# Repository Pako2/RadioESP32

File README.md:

# RadioESP32
RadioESP32 is a high-performance multimedia platform built on the ESP32 architecture. Originally starting as a dedicated standalone internet radio, the platform has evolved significantly. Starting with version 2.0.0, the project has been completely re-engineered into an advanced multi-boot system that transforms a single hardware device into an Internet Radio player, a local SD card audiobook player, and a high-fidelity Bluetooth loudspeaker – all managed by an independent recovery and deployment application.\
**Note:** Complete project documentation can be found in the [UserGuide_EN.pdf](doc/UserGuide_EN.pdf) file.

### Display and embedded web server preview
For illustration, you can see three photos of the display. You may be surprised to see that some of the text lines are blurred. The explanation is simple. This is scrolling text, because otherwise it wouldn't fit on the display!\
The first picture shows the radio playing, the second shows a file playing from an SD card, and the third shows the clock.

There's no need to describe the appearance of the web interface. You can learn much more from a few screenshots.

## Project Origin & Acknowledgments
This project would likely never have been created without the popular [ESP32Radio-V2](https://github.com/Edzelf/ESP32Radio-V2) project by [Edzelf](https://github.com/Edzelf). I am deeply grateful to the author for his outstanding work, which served as the original foundation for this software.

While I initially deployed the original project in its unchanged form, several limitations quickly became apparent. My primary motivation for rewriting and expanding the software stemmed from two major issues:

- **Localization:** The original display implementation did not support accented diacritics, which was critical for a proper local user experience.

- **Audiobook Playback:** One of my core requirements was the ability to listen to audiobooks from an SD card. Audiobooks require files to be played in a strict, defined alphabetical order. In the original software, copying files from a PC to an SD card resulted in them being indexed and played in a seemingly random order, making sequential listening highly complicated without constant manual track selection.

Additionally, I preferred a different default behavior. Instead of always resuming the last played station at the previous volume level upon power-up, I prefer the device to initialize to a pre-defined default station and default volume. I also planned to integrate entirely new hardware and software features, such as single-button power toggling and an automated sleep/turn-off timer.

Despite these changes, several core elements from Edzelf's project were retained, which significantly aided my early development. Furthermore, the web interface design, the communication method between the ESP32 and the browser, and the configuration file management system were adopted from the [esp-rfid](https://github.com/esprfid/esp-rfid) project - a highly reliable setup I have successfully utilized across multiple designs.

# Evolution in Version 2.0.0+
During development, I realized that with a purely software-driven approach, the existing hardware design could be utilized as a full-featured Bluetooth loudspeaker. To implement this comfortably, version 2.0.0 underwent a fundamental architectural overhaul.
To streamline production and focus on maximum stability, legacy sub-variants (such as designs without a display or designs storing web server assets directly inside a volatile file system partition) were abandoned. Moving forward, the project is maintained as a single production variant: always equipped with a display and always compiling web server assets directly into the program memory. This specific design is mandatory to support the automated multi-boot Update Manager system.

## Upgrading from Version 1.X.X
If you are upgrading an existing device from a 1.X.X release, your configuration file is fully compatible with the new version. However, due to the fundamental architectural changes mentioned above, a clean installation via cable is required:
- **Backup** your current configuration using the Backup & Restore menu in your existing web interface.
- Perform a **full installation** over a USB cable using the new Flash utility (flash.bat).
- **Restore** your configuration file using the Backup & Restore menu in the new version 2.0.0 interface.

**Note:** 
*Before proceeding with the upgrade, please verify that your hardware meets the new minimum requirements (8MB Flash and PSRAM), as legacy 4MB modules are no longer supported.*

## Legacy Differences: Radio Application vs. Edzelf's ESP32Radio
The following enhancements and modifications apply exclusively to the Internet Radio application (and its web configuration) compared to the original Edzelf implementation:

- **Strict Alphabetical Playback:** Fixed the random indexing issue on SD cards. Files and folders are sorted properly, enabling seamless audiobook listening. However, shuffle mode can be turned on as needed.

- **Diacritics & Extended Character Support:** The display engine was rewritten to support full native character mapping and custom fonts.

- **Predictable Initialization:** The device turns on to a user-defined default station and safe volume level rather than resuming the last state.

- **Single-Button Power Toggle:** Hardware-software integration allows turning the entire device completely on and off using the same single physical button.

- **Integrated Sleep Timer:** Supports a configurable sleep countdown that automatically powers down the hardware.

- **Comfortable Web-Based IR Learning:** Unlike the original project, adding or modifying infrared remote control commands is managed through an incredibly intuitive and automated web interface, allowing the device to capture and assign raw hardware codes on the fly.

# Full-Featured Bluetooth Loudspeaker Application
The Bluetooth Loudspeaker mode (running on OTA\_1) is engineered to deliver a premium commercial-grade user experience, offering deep visual feedback and control options rarely found in DIY audio systems.

## Key features include:
- **Identical Display Dashboard:** The physical display mirrors the rich visual interface of the Radio application, showing a real-time battery status indicator, an active volume bar, and a track progress bar.

- **Dynamic Status Icons:** Features clear visual indicators for Bluetooth connectivity (color-coded blue for active connection, grey for disconnected state) along with dedicated Play/Pause status indicators.

- **Rich Metadata & Auto-Scrolling:** Streams live metadata directly from the connected smartphone. Track titles, artist names, and album details are fully processed and rendered with native diacritic support, automatically triggering a smooth text-scrolling engine if the text length exceeds the screen boundaries.

- **Dual Physical Control Layers:** The loudspeaker can be controlled fully via the mechanical physical rotary encoder or completely hands-free using an Infrared Remote Control (handling Play, Pause, Track Skip, and Volume adjustments).

- **Centralized Configuration:** Because the Bluetooth application completely turns off the Wi-Fi stack to eliminate protocol overhead and interference, it does not host a web server. Instead, all Bluetooth-specific settings (including custom broadcast device naming and the advanced IR remote control command learning) are comfortably configured inside the unified web interface of the Internet Radio application.

# System Architecture & Multi-Boot Partitioning
Due to the strict hardware limitations of the ESP32 chip (specifically the high instability and memory constraints of running Wi-Fi and Bluetooth stacks simultaneously) the system separates core features into completely independent firmware binaries.

The system utilizes a custom partition layout designed for 8MB Flash chips. The minimum required hardware configuration is the ESP32-WROVER-E-N8R4 module. Volatile PSRAM memory is mandatory, as modern versions of the underlying audio libraries will not function without it.

## The memory layout divides the hardware into four distinct primary zones:
| Partition Type | Application Name | Core Functionality | Network State |
| - | - | - | - |
| **Factory** | Update Manager | Recovery, deployment, and binary flashing | Wi-Fi (Station with Internet) |
| **OTA\_0** | Internet Radio | Web-streaming, SD card media player | Wi-Fi (Station / Initial AP Setup) |
| **OTA\_1** | BT Loudspeaker | High-fidelity A2DP audio playback | Completely Disabled (No Wi-Fi) |
| **LittleFS** | Configuration | Shared system settings and profiles | Non-volatile storage |

All three applications share a single, unified configuration file stored in the LittleFS zone. Switching between applications triggers a low-level hardware reset using direct RTC controller registry manipulation, ensuring that the hardware cache and DMA controllers are completely cleared for a pure warm boot.

# Independent Update Manager
Because individual OTA application partitions contain completely different binary structures (Radio vs. Bluetooth), traditional OTA upgrades (where a new version is uploaded to an inactive slot and toggled) are impossible.

The project solves this by deploying a completely independent recovery application in the factory partition. When triggered via the display menu or the radio's web interface, the device reboots into the red-themed Update Manager web server (accessible via the credentials defined in the source code). From this dashboard, users can view live tables comparing current firmware versions against the latest versions available online, perform automated network updates, create full system binary backups, or deploy manual downgrades from local files.

### ⚠️ Important Note regarding Over-the-Air (OTA) Web Upgrades

Due to strict modern browser security standards (CORS policies) implemented by GitHub, web browsers will natively block the JavaScript interface from directly transferring firmware files from GitHub Releases onto your local IP address via the single-click "Update" buttons.

To complete an application upgrade, you have two equally reliable options:

1. **Manual Offline Upload (Recommended & Safest):** 
   Simply click the green **Download** button next to the target application to save the latest `.bin` firmware file directly to your PC. Then, navigate to the **Firmware Upload** panel below, select the correct **Target Application**, click the **Browse...** button to select the downloaded binary from your hard drive, and click **Flash Selected File**.

2. **Direct Web Upgrade (Advanced):**
   If you prefer to upgrade with a single click directly from the web interface using the automated table, you must temporarily enable a CORS-bypass extension in your browser (such as *"Allow CORS: Access-Control-Allow-Origin"* for Chrome/Firefox) before opening the Update Manager dashboard.

The Update Manager features critical system-level fail-safes. If the supply battery drops below a safe operational threshold during an update cycle, an asynchronous JavaScript modal hard-locks the entire web interface, preventing user interactions until safe power parameters are restored, eliminating the risk of accidental firmware bricking.

## Advanced Graphics Engineering
To achieve absolute long-term stability, the graphics pipeline was completely refactored. The Bluetooth application runs an aggressive real-time A2DP data sink. Under standard implementations, multi-core thread collisions frequently occur on the shared SPI display bus when high-priority Bluetooth background tasks on Core 0 interrupt the main application execution loop on Core 1.

The system eliminates these race conditions by removing traditional RTOS mutexes entirely. Instead, all graphic subsystems, status readouts, and display bars (such as the volume bar, battery indicator, progress bars, and scrolling metadata tracks) are completely centralized under a single-task, asynchronous flag-driven pipeline in the display loop. Asynchronous events from Bluetooth callbacks merely flag status variables in RAM, which are safely ingested and drawn by a single dedicated display task.

# Development and Build Flags
The project is developed in VS Code using the PlatformIO IDE paired with the Pioarduino extension. Using environment build flags in `platformio.ini`, the firmware behavior is customized using the following core definitions:

- **DATAWEB=true/false:** Setting this flag to `true` compiles a development variant where web server assets are loaded dynamically from the LittleFS partition, allowing real-time, browser-based source editing via the integrated online [Ace editor](https://ace.c9.io/). Setting this to `false` creates the production variant, compressing and injecting all HTML and JS assets directly into the program memory (PROGMEM) as static variables. This is the mandatory format for deployment binaries.

- **SDCARD:** Compiles full support for the local SD card hardware and alphabetical media player engine.

- **BATTERY:** Enables power monitoring, enabling precise voltage calibration routines and rendering live battery status bars across both the physical display and web dashboards.

- **AUTOSHUTDOWN:** Compiles the control logic for the single-button soft power toggle circuit and the automatic sleep timer.

# Third-Party Libraries & Acknowledgments
This project relies heavily on the open-source community. I would like to express my sincere gratitude to the authors of the following exceptional libraries, whose hard work made this multi-boot platform possible:

- **[ESP32-audioI2S](https://github.com/schreibfaul1/ESP32-audioI2S) by schreibfaul1** – The core engine powering the high-performance internet radio streaming and SD card media playback.

- **[ESP32-A2DP](https://github.com/pschatzmann/ESP32-A2DP) by pschatzmann** – The backbone of the Bluetooth application, providing a reliable and robust real-time A2DP audio sink.

- **[ESPAsyncWebServer](https://github.com/ESP32Async/ESPAsyncWebServer)** – Essential for driving the asynchronous, responsive web interfaces across the platform slots.

- **[ArduinoJson](https://github.com/bblanchon/ArduinoJson) by bblanchon** – Used for fast, memory-efficient parsing of configuration files and the update manager tables.

- **[base64](https://github.com/Densaugeo/base64_arduino) by Densaugeo** – Utilized for secure encoding and handling of system assets and network communication data.

- **[Arduino-IRremote](https://github.com/Arduino-IRremote/Arduino-IRremote)** – Powering the automated infrared remote control receiver and code-learning capabilities.

- **[TFT\_eSPI](https://github.com/Bodmer/TFT_espi) by Bodmer** – The highly optimized graphics driver used to render sprites and smooth scrolling text on the SPI display.

- **[U8g2](https://github.com/olikraus/u8g2) by olikraus** & **[U8g2\_for\_TFT\_eSPI](https://github.com/Bodmer/U8g2_for_TFT_eSPI) by Bodmer** – Providing the comprehensive font support required for native localization, accented diacritics, and system icons.

## PlatformIO Environment & Custom Python Targets
The project utilizes advanced customization features of PlatformIO with the Pioarduino extension to automate the compilation, transformation, and deployment of firmware slots. Since standard environment filters naturally restrict automated serial flashing to the `OTA_0` partition, a dedicated set of specialized automation scripts was engineered to streamline the development workflow:

- **`app_deploy.py` (Binary Archiving):** Executed automatically post-build. It automatically moves and renames compiled images into the structured `/bin/<env>/` directory, preparing them for deployment.

- **`custom_targets.py` (Advanced Workflow Automation):** Exposes core system functions accessible comfortably directly via the *Pioarduino: Project Tasks / \<env\> / Custom* IDE side menu. It processes two critical automated workflows:

  - **Download FS & Create WEBH:** Automates the complete transformation of production web assets. It downloads the live file system image from the hardware using maxgerhardt's downloader utility, extracts the HTML and JS assets from `LittleFS`, and translates them directly into compressed C++ array data variables ready for `PROGMEM` generation.

  - **Upload custom binary:** The primary development flashing mechanism. Instead of pushing blindly to `OTA_0`, this target programmatically parses the local partition configuration table, dynamically locates the precise memory address boundaries for the active target environment, and executes a targeted wired upload directly to the correct slot (`OTA_1` for Bluetooth loudspeaker or `factory` for the Update Manager).

## Production Flash Utilities
For initial provisioning, assembly, and bulk deployment outside the VS Code IDE development sandbox, a dedicated, standalone host script named Flash Utilities is used.

This standalone batch utility operates strictly as a master installation tool tailored for two main deployment scenarios:

1. **Full Environment Initialization:** Performs the first-time wired flashing of a fresh, raw ESP32 chip. It writes the global bootloader configurations, custom multi-boot partition boundaries, the initial `LittleFS` shared configuration image, and all three application binaries concurrently.

2. **Targeted Service Upgrades:** Provides a safe serial bypass tool to manually write or restore a single specific slot over a wired serial connection. This is the mandatory path required for initial installation or forced rewrites of the factory recovery application partition without formatting or impacting user profiles.

On a fresh device provisioning cycle, the system triggers a default fallback standalone Wi-Fi Access Point named **RadioESP32**. Navigating a web browser to `192.168.4.1` loads the initial onboarding setup screen to connect the multi-boot hardware platform to local wireless station configurations.

# Hardware Design & Component Selection
The physical hardware architecture is designed using the free/personal-use tier of Autodesk Eagle, utilizing a dual-stage isolation approach to completely eliminate ground loops, digital switching noise, and interference.

### Wiring diagram

### Printed circuit board

### Choice of components
In the first phase of development, I used the VS1053 module (as a DAC) following Edzelf's example. It worked well, but I found this solution unnecessarily expensive and quite problematic (for example, I once accidentally bought a VS1003 instead and it didn't work well). That's why I completely abandoned this path and switched exclusively to a solution with I2S.
- **Main Processor:** ESP32-WROVER-E module (Silicon Revision 3 or higher, minimum 8MB Flash and 4MB PSRAM).

- **Power Supply:** 12V primary input, optimized to run efficiently from three series-connected 18650 Li-ion cells or a standard wall adapter. A high-efficiency Mini560 step-down module regulates this down to a stable 5V rail. The module's EN (Enable) pin is directly wired into the single-button latching circuit for hard physical power management.

- **Audio DAC:** PCM5102A I2S module, selected for its high dynamic range and integrated analog out pin liars, eliminating complex internal chassis cabling.

- **Ground Loop Isolation:** Two low-profile 9.1mm audio isolation transformers are placed inline directly between the DAC outputs and the amplifier inputs, successfully blocking digital hum and cross-talk.

- **Amplifier Stage:** PAM8406 5V stereo amplifier IC. This specific chip was chosen because it can operate in either Class-D (high efficiency for battery operation) or Class-AB (low RF noise for clean radio reception). The operating mode is manually selected on the PCB via hardware jumpers.

- **Display Interface:** 1.77-inch SPI TFT panel (160x128 resolution) driven natively by the optimized TFT\_eSPI library.

- **User Control:** A robust EC11 mechanical rotary encoder with an integrated push-button handles physical navigation, complemented by a VS1838B infrared receiver supporting automatic remote control code learning.

- **Chassis Connections:** Traditional screw terminals were replaced with high-reliability 4.8mm male Faston terminals soldered directly to the PCB for all primary power inputs and speaker outputs, ensuring vibrating-proof connections inside the speaker enclosure.

## Assembled board
Finally, you can see a few pictures of the printed circuit board completely assembled and including the installed subboards (ESP32 development kit and DAC). I also added one photo of the finished radio (powered by three 18650 Li-ion cells).

### License
The code parts written by the author of the **RadioESP32** project are licensed under [GPL-3.0](LICENSE), 3rd party libraries that are used by this project are licensed under different license schemes, please check them out as well.

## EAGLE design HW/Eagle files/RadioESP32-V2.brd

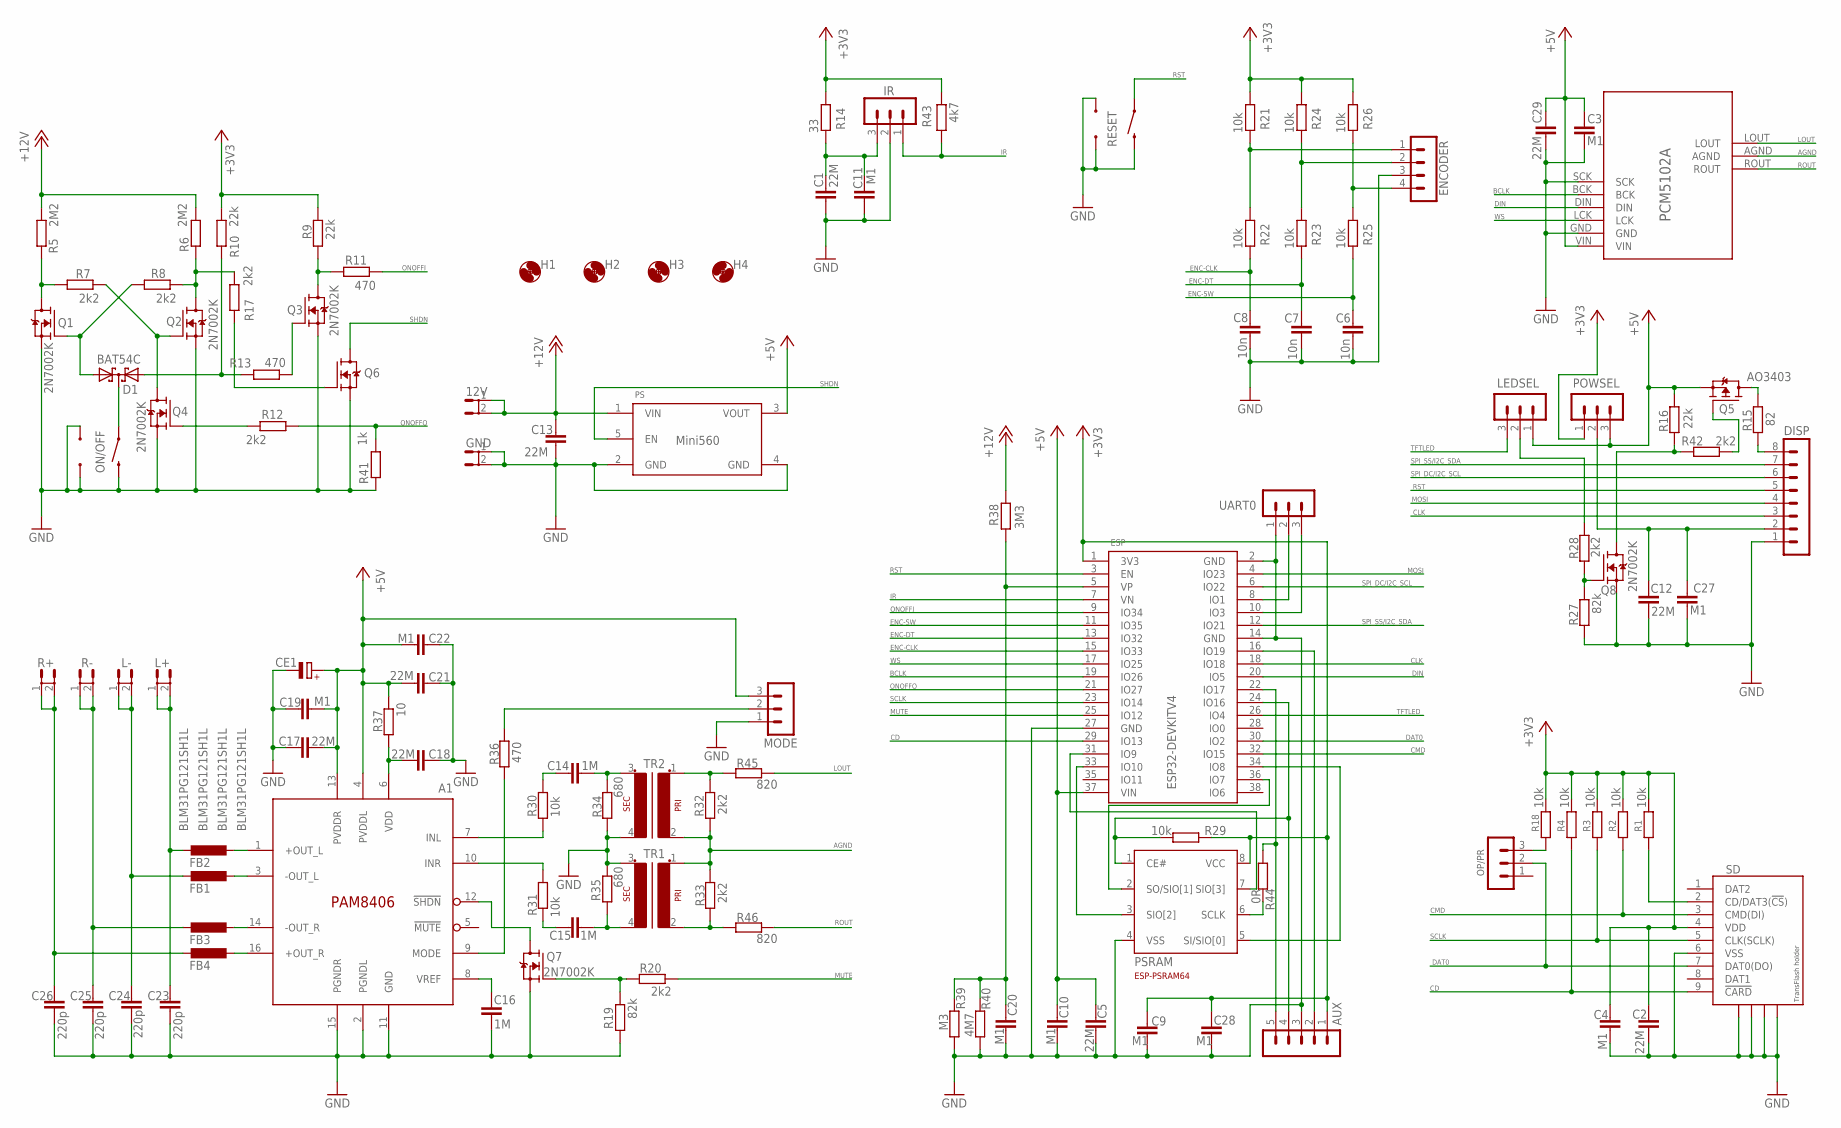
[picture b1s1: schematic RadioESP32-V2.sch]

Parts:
12V: FASTON; FASTON4.8
A1: PAM8406; SOP-16
AUX: CON-LSTB_MA05-108; CON-LSTB_MA05-1-NS08
C1, C2, C5, C12, C13, C17, C18, C21, C29: 22M; C1206K
C3, C4, C9, C10, C11, C19, C20, C22, C27, C28: M1; C0805
C6, C7, C8: 10n; C0805
C14, C15, C16: 1M; C1206K
C23, C24, C25, C26: 220p; C0805
CE1: CPOL; E5-10.5
D1: BAT54C; SOT23
DISP: CON-LSTB_MA08-108; CON-LSTB-MA08-1-NS08
ENCODER: CON-LSTB_MA04-108; CON-LSTB_MA04-1-NS08
ESP: ESP32-DEVKITV4_ESP32DEVKITV4NOTXT; ESP32_DEVKIT_V4
FB1, FB2, FB3, FB4: BLM31PG121SH1L; C1206K
GND: FASTON; FASTON4.8
H1, H2, H3, H4: MOUNT-HOLE3.0; 3,0
IR: CON-LSTB_MA03-108; CON-LSTB_MA03-1-NS08
L+: FASTON; FASTON4.8
L-: FASTON; FASTON4.8
LEDSEL: CON-LSTB_MA03-108; CON-LSTB_MA03-1-NS08
MODE: CON-LSTB_MA03-108; CON-LSTB_MA03-1-NS08
ON/OFF: MOMENTARY-SWITCH-SPST1; TACTILE_SWITCH_ANGLE-NS1
OP/PR: CON-LSTB_MA03-108; CON-LSTB_MA03-1-NS08
PCM5102A: PCM5102A_MODULE
POWSEL: CON-LSTB_MA03-108; CON-LSTB_MA03-1-NS08
PS: MINI560EXT; MINI560-NS-EXT
PSRAM: PSRAM; SOT23-8-W
Q1, Q2, Q3, Q4, Q6, Q7, Q8: 2N7002K; TRANSISTOR-FET_SOT23
Q5: AO3403; SOT23
R1, R2, R3, R4, R18, R21, R22, R23, R24, R25, R26, R29, R30, R31: 10k; R0805
R5, R6: 2M2; R0805
R7, R8, R12, R17, R20, R28, R32, R33, R42: 2k2; R0805
R9, R10, R16: 22k; R0805
R11, R13, R36: 470; R0805
R14: 33; R0805
R15: 82; R1206
R19, R27: 82k; R0805
R34, R35: 680; R0805
R37: 10; R0805
R38: 3M3; R0805
R39: M3; R0805
R40: 4M7; R0805
R41: 1k; R0805
R43: 4k7; R0805
R44: 0R; R0805
R45, R46: 820; R0805
R+: FASTON; FASTON4.8
R-: FASTON; FASTON4.8
RESET: MOMENTARY-SWITCH-SPST1; TACTILE_SWITCH_ANGLE-NS1
SD: SD-MMC_TF-HOLDER; SD-MMC_TF-PULL
TR1, TR2: AUDIOTRAFONS2; AUDIOTRAFO_2-NS
UART0: CON-LSTB_MA03-108; CON-LSTB_MA03-1-NS08

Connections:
+3V3: AUX.1, C2.2, C4.2, C9.2, C28.2, ESP.1 (3V3), POWSEL.1, PSRAM.8 (VCC), R1.2, R2.2, R3.2, R4.2, R9.2, R10.2, R14.2, R18.2, R21.2, R24.2, R26.2, R29.1, R43.1, SD.4 (VDD)
+5V: A1.4 (PVDDL), A1.13 (PVDDR), C3.1, C5.1, C10.1, C17.2, C19.2, C21.1, C22.1, C29.2, CE1.+, CE1.++ (+), ESP.37 (VIN), LEDSEL.1, MODE.3, PCM5102A.VIN, POWSEL.3, PS.3 (VOUT), Q5.2 (S), R16.2, R37.1
+12V: 12V.1, 12V.2, C13.2, PS.1 (VIN), R5.2, R6.2, R38.2
AGND: PCM5102A.AGND, R32.1, R33.2, TR1.1, TR2.2
BCLK: ESP.19 (IO26), PCM5102A.BCK
CD: ESP.29 (IO13), R4.1, SD.9 (!CARD)
CLK: DISP.3, ESP.18 (IO18)
CMD: ESP.32 (IO15), R2.1, SD.3 (CMD(DI))
DAT0: ESP.30 (IO2), OP/PR.2, SD.7 (DAT0(DO))
DIN: ESP.20 (IO5), PCM5102A.DIN
ENC-CLK: C8.1, ESP.15 (IO33), R22.1
ENC-DT: C7.1, ESP.13 (IO32), R23.1
ENC-SW: C6.1, ESP.11 (IO35), R25.1
GND: A1.2 (PGNDL), A1.11 (GND), A1.15 (PGNDR), AUX.3, C1.2, C2.1, C3.2, C4.1, C5.2, C6.2, C7.2, C8.2, C9.1, C10.2, C11.2, C12.1, C13.1, C16.1, C17.1, C18.2, C19.1, C20.1, C21.2, C22.2, C23.1, C24.1, C25.1, C26.1, C27.2, C28.1, C29.1, CE1.-, DISP.1, ENCODER.3 (4), ESP.2 (GND), ESP.14 (GND), ESP.27 (GND), GND.1, GND.2, IR.2, MODE.1, ON/OFF.2, ON/OFF.A1, ON/OFF.A2, PCM5102A.GND, PCM5102A.SCK, PS.2 (GND), PS.4 (GND), PSRAM.4 (VSS), Q1.2 (S), Q2.2 (S), Q3.2 (S), Q4.2 (S), Q6.2 (S), Q7.2 (S), Q8.2 (S), R19.2, R27.2, R34.1, R35.2, R39.1, R40.1, R41.1, RESET.2, RESET.A1, RESET.A2, SD.6 (VSS), SD.S1, SD.S2, SD.S3, SD.S4, TR1.3 (S1), TR2.4 (S2), UART0.1
IR: ESP.7 (VN), IR.1, R43.2
LEDA: DISP.8, R15.1
LOUT: PCM5102A.LOUT, R45.2
MOSI: DISP.4, ESP.4 (IO23)
MUTE: ESP.25 (IO12), R20.1
N31: D1.2 (A2), R10.1, R13.2
unnamed: ESP.36 (IO7), PSRAM.2 (SO/SIO[1])
unnamed: ESP.34 (IO8), PSRAM.5 (SI/SIO[0])
unnamed: C14.1, R34.2, TR2.3 (S1)
unnamed: C15.2, R35.1, TR1.4 (S2)
unnamed: C14.2, R30.2
unnamed: A1.7 (INL), R30.1
unnamed: C15.1, R31.2
unnamed: A1.10 (INR), R31.1
unnamed: C1.1, C11.1, IR.3, R14.1
unnamed: Q2.3 (D), R6.1, R8.1, R17.1
unnamed: Q7.1 (G), R19.1, R20.2
unnamed: ESP.33 (IO10), PSRAM.3 (SIO[2])
unnamed: ESP.31 (IO9), PSRAM.7 (SIO[3])
unnamed: Q3.1 (G), R13.1
unnamed: R1.1, SD.2 (CD/DAT3(!CS!))
unnamed: Q1.3 (D), R5.1, R7.2
unnamed: Q5.1 (G), R42.1
unnamed: D1.3 (CC), ON/OFF.1
unnamed: Q2.1 (G), Q4.3 (D), R7.1
unnamed: D1.1 (A1), Q1.1 (G), R8.2
unnamed: Q4.1 (G), R12.2
unnamed: AUX.4, ESP.24 (IO16), PSRAM.1 (CE#), R29.2
unnamed: Q3.3 (D), R9.1, R11.2
unnamed: PSRAM.6 (SCLK), R44.2
unnamed: AUX.2, ESP.16 (IO19)
unnamed: C12.2, C27.1, DISP.2, POWSEL.2
unnamed: R32.2, R45.1, TR2.1
unnamed: A1.8 (VREF), C16.2
unnamed: A1.12 (!SHDN), Q7.3 (D)
unnamed: A1.9 (MODE), R36.1
unnamed: MODE.2, R36.2
unnamed: C23.2, FB2.2, L+.1, L+.2
unnamed: R33.1, R46.1, TR1.2
unnamed: C25.2, FB3.2, R-.1, R-.2
unnamed: C26.2, FB4.2, R+.1, R+.2
unnamed: A1.1 (+OUT_L), FB2.1
unnamed: A1.3 (-OUT_L), FB1.1
unnamed: A1.14 (-OUT_R), FB3.1
unnamed: A1.16 (+OUT_R), FB4.1
unnamed: Q5.3 (D), R15.2
unnamed: Q8.3 (D), R16.1, R42.2
unnamed: OP/PR.3, R18.1
unnamed: C20.2, ESP.5 (VP), R38.1, R39.2, R40.2
unnamed: Q6.1 (G), R17.2
unnamed: C24.2, FB1.2, L-.1, L-.2
unnamed: ENCODER.4 (5), R25.2, R26.1
unnamed: ENCODER.2 (3), R23.2, R24.1
unnamed: ENCODER.1 (2), R21.1, R22.2
unnamed: Q8.1 (G), R27.1, R28.1
ONOFFI: ESP.9 (IO34), R11.1
ONOFFO: ESP.21 (IO27), R12.1, R41.2
ROUT: PCM5102A.ROUT, R46.2
RST: DISP.5, ESP.3 (EN), RESET.1
RX: ESP.10 (IO3), UART0.3
SCLK: ESP.23 (IO14), R3.1, SD.5 (CLK(SCLK))
SHDN: PS.5 (EN), Q6.3 (D)
SPI_DC/I2C_SCL: DISP.6, ESP.6 (IO22)
SPI_SS/I2C_SDA: DISP.7, ESP.12 (IO21)
TFTG: LEDSEL.2, R28.2
TFTLED: ESP.26 (IO4), LEDSEL.3
TX: ESP.8 (IO1), UART0.2
VDD: A1.6 (VDD), C18.1, R37.2
WS: ESP.17 (IO25), PCM5102A.LCK
XDCS: AUX.5, ESP.22 (IO17), R44.1

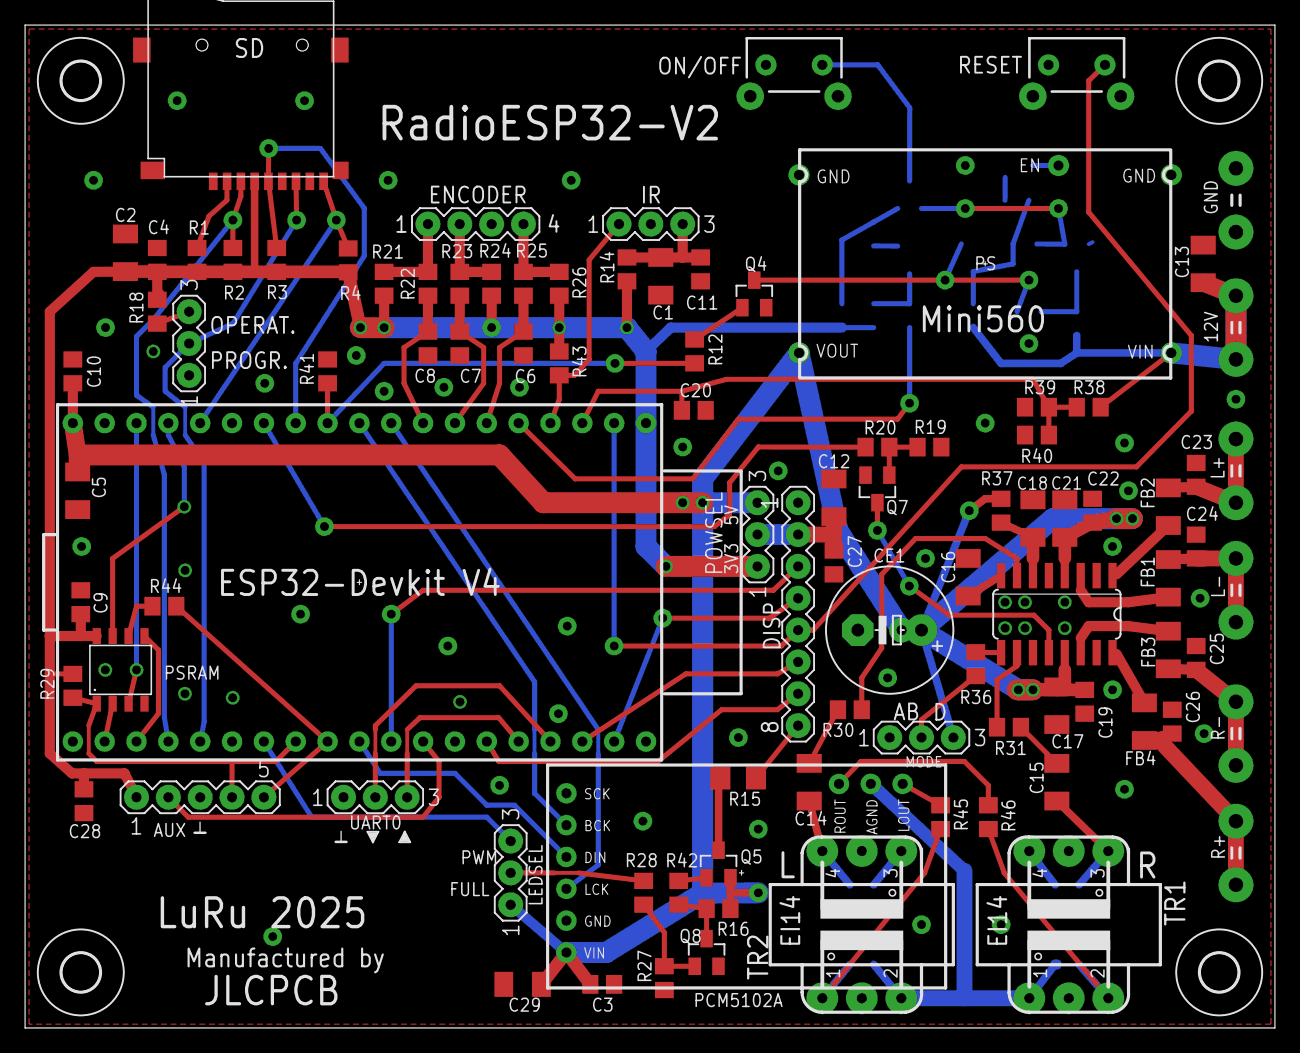
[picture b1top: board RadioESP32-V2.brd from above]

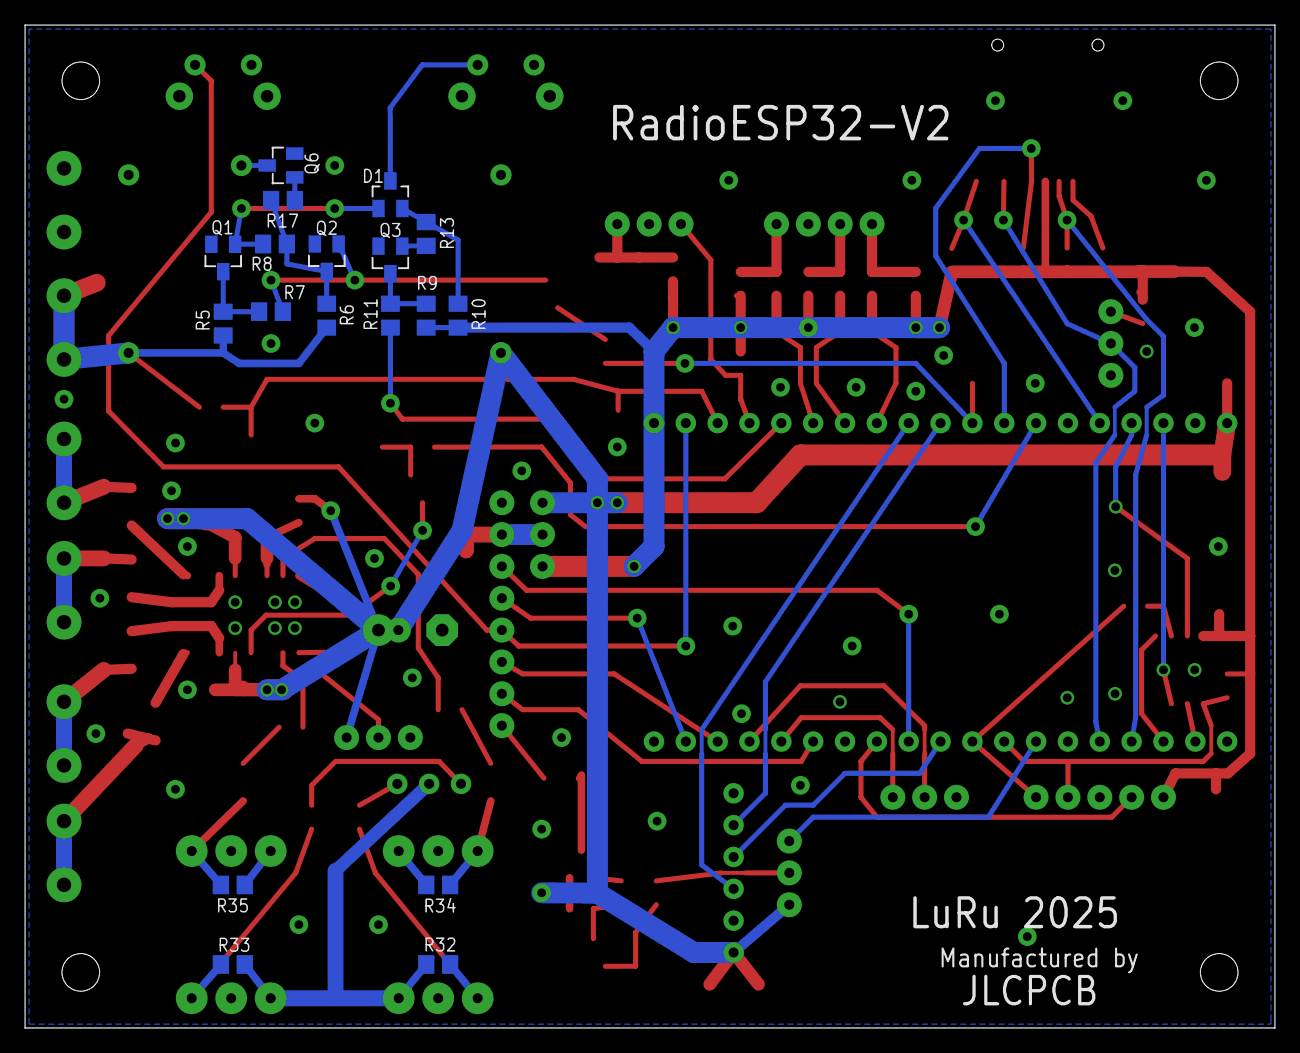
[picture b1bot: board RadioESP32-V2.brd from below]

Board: 2 copper layers, 99.7 x 80.0 mm, 118 parts (18 on the bottom side), 84 nets.

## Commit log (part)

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2025-02-28 first public version
2025-02-28 README.md update
2025-03-01 platformio.ini update
2025-03-01 adc1_0__bugfix
2025-03-02 1.0.2
2025-03-05 1.0.3
2025-03-13 1.0.4
2025-03-16 1.0.5
2025-03-19 1.0.6
2025-05-22 1.0.7

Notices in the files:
README.md:
License:
The code parts written by the author of the **RadioESP32** project are licensed under [GPL-3.0](LICENSE), 3rd party libraries that are used by this project are licensed under different license schemes, please check them out as well.
